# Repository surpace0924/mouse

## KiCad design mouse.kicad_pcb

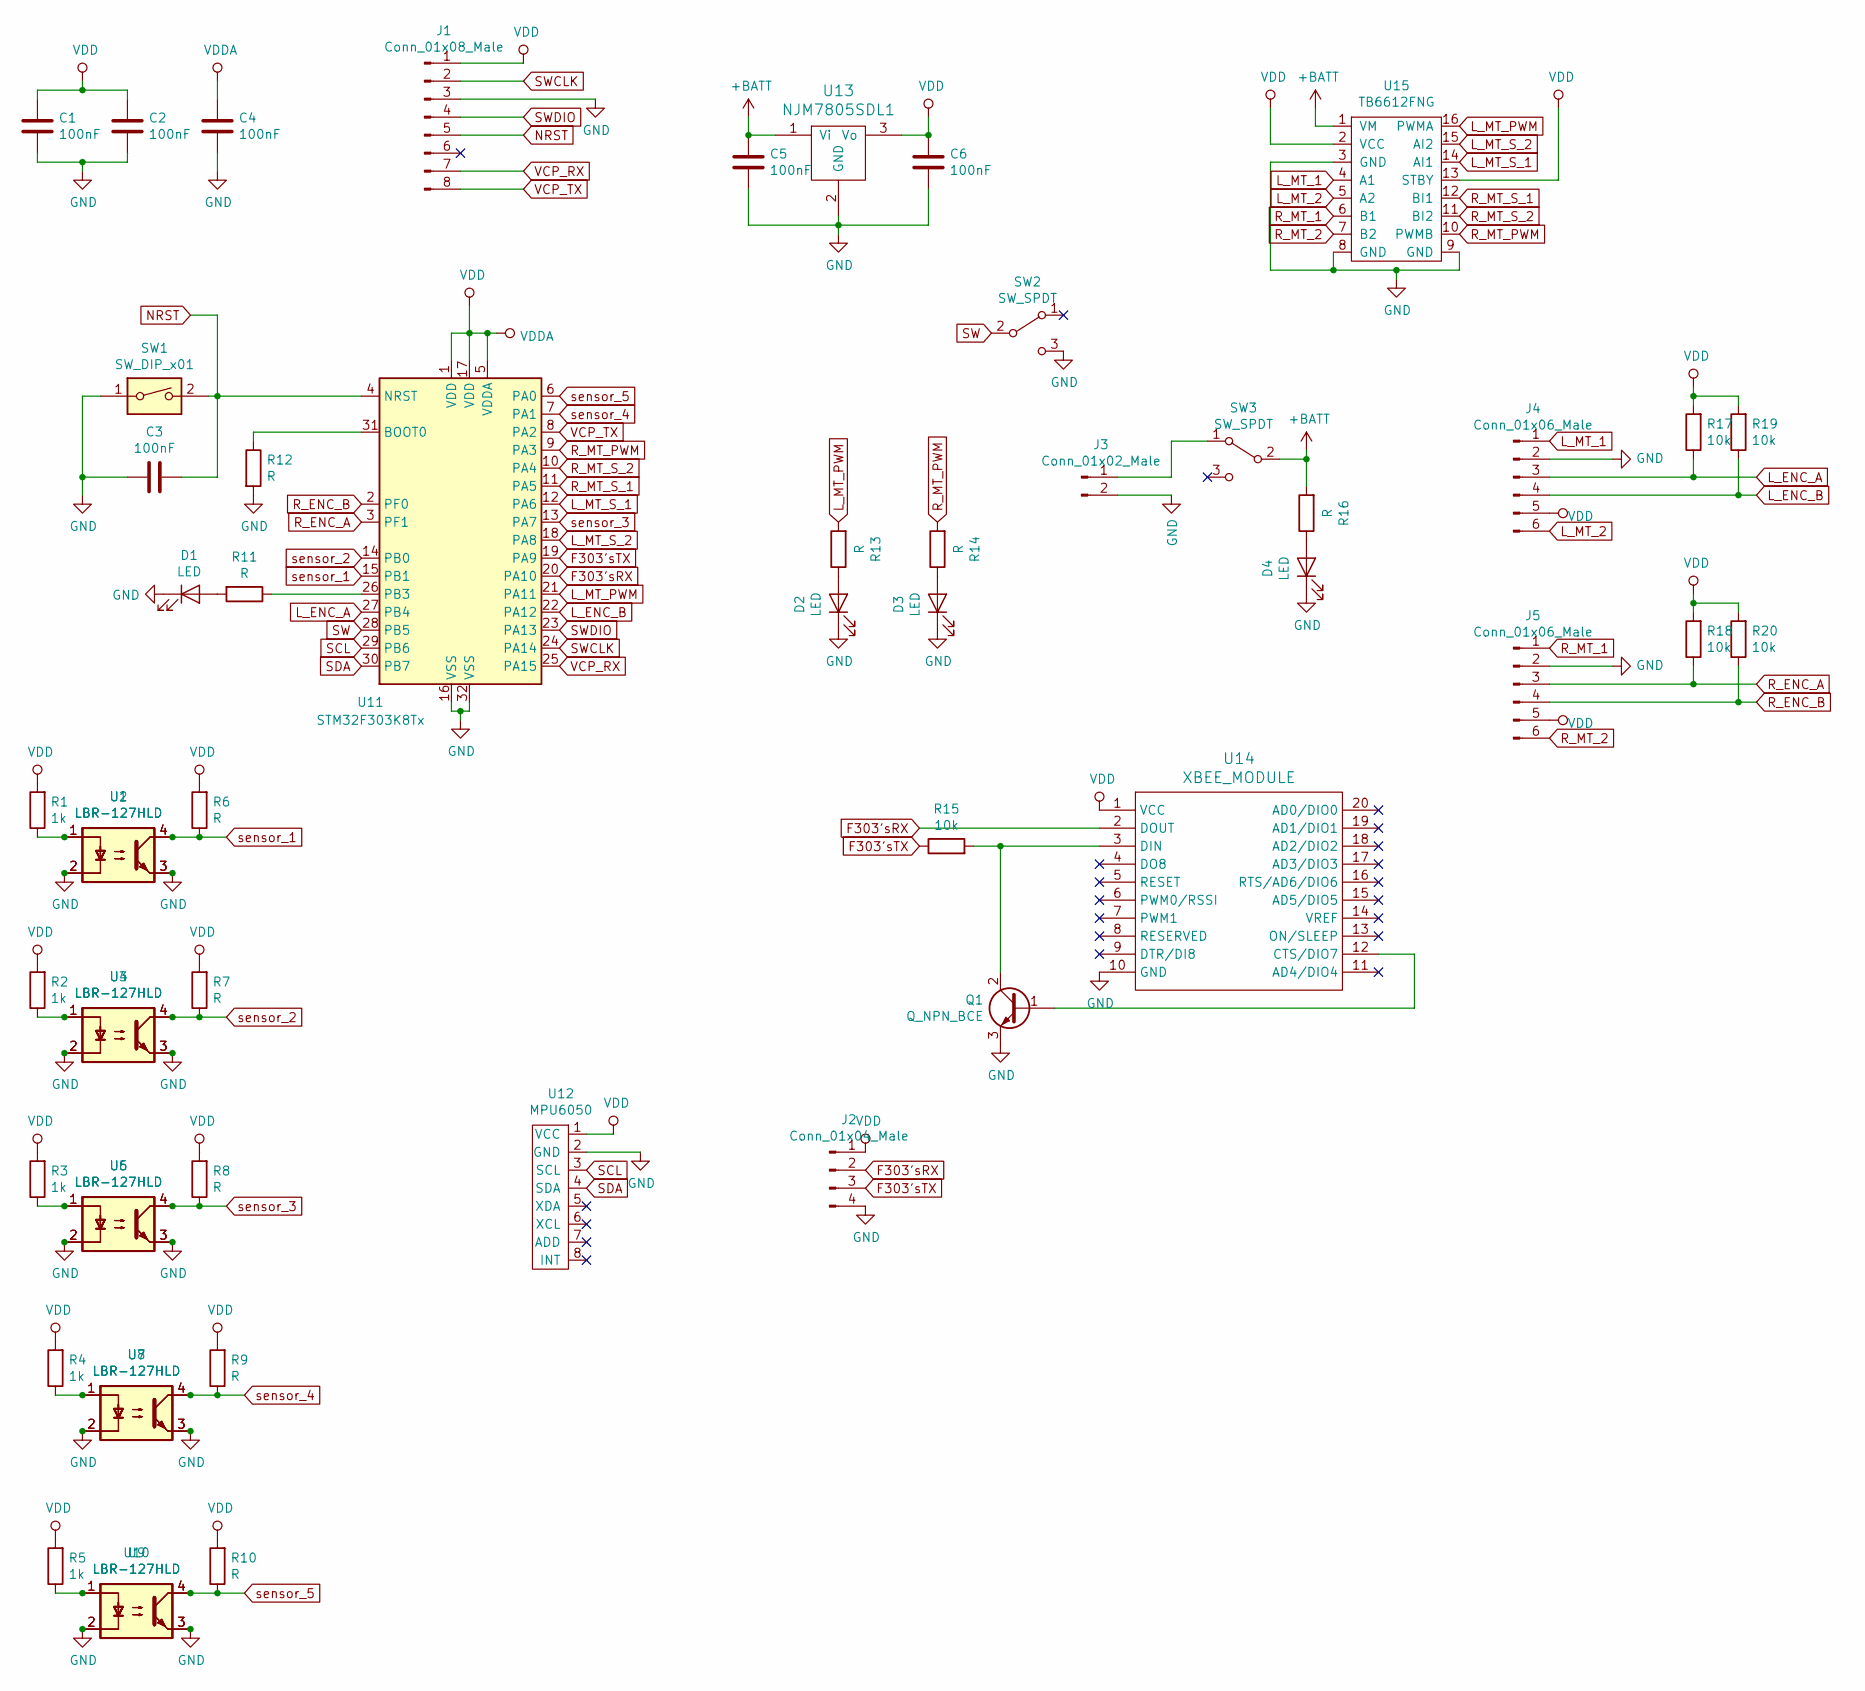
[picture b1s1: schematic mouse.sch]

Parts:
C1, C2, C3, C4, C5, C6: 100nF; C_0805_2012Metric_Pad1.15x1.40mm_HandSolder
D1, D2, D3, D4: LED; LED_0603_1608Metric
J1: Conn_01x08_Male; PinSocket_1x08_P2.54mm_Vertical
J2: Conn_01x04_Male; JST_XH_B4B-XH-A_1x04_P2.50mm_Vertical
J3: Conn_01x02_Male; JST_XH_B2B-XH-A_1x02_P2.50mm_Vertical
J4, J5: Conn_01x06_Male; PinSocket_1x06_P2.54mm_Vertical
Q1: Q_NPN_BCE; TO-92Flat
R1, R2, R3, R4, R5: 1k; R_0603_1608Metric_Pad1.05x0.95mm_HandSolder
R6, R7, R8, R9, R10: R; R_Axial_DIN0204_L3.6mm_D1.6mm_P7.62mm_Horizontal
R11, R12, R13, R14, R16: R; R_0603_1608Metric_Pad1.05x0.95mm_HandSolder
R15, R17, R18, R19, R20: 10k; R_0603_1608Metric_Pad1.05x0.95mm_HandSolder
SW1: SW_DIP_x01; SW_PUSH_6mm_H4.3mm
SW2, SW3: SW_SPDT; PinSocket_1x03_P2.54mm_Vertical
U1, U2, U3, U4, U5, U6, U7, U8, U9, U10: LBR-127HLD; LBR-127HLD_2
U11: STM32F303K8Tx; LQFP-32_7x7mm_P0.8mm
U12: MPU6050; MPU6050_2
U13: NJM7805SDL1; TO-252-3_TabPin2
U14: XBEE_MODULE; XBee
U15: TB6612FNG

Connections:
+BATT: C5.2, R16.2, SW3.2 (B), U13.1 (Vi), U15.1 (VM)
F303'sRX: J2.2, U11.20 (PA10), U14.2 (DOUT)
F303'sTX: J2.3, R15.1, U11.19 (PA9)
GND: C1.1, C2.1, C3.2, C4.1, C5.1, C6.1, D1.1 (K), D2.1 (K), D3.1 (K), D4.1 (K), J1.3, J2.4, J3.2, J4.2, J5.2, Q1.3 (E), R12.2, SW1.1, SW2.3 (C), U1.2, U1.3, U2.2, U2.3, U3.2, U3.3, U4.2, U4.3, U5.2, U5.3, U6.2, U6.3, U7.2, U7.3, U8.2, U8.3, U9.2, U9.3, U10.2, U10.3, U11.16 (VSS), U11.32 (VSS), U12.2 (GND), U13.2 (GND), U14.10 (GND), U15.3 (GND), U15.8 (GND), U15.9 (GND)
L_ENC_A: J4.3, R17.1, U11.27 (PB4)
L_ENC_B: J4.4, R19.1, U11.22 (PA12)
L_MT_1: J4.1, U15.4 (A1)
L_MT_2: J4.6, U15.5 (A2)
L_MT_PWM: R13.2, U11.21 (PA11), U15.16 (PWMA)
L_MT_S_1: U11.12 (PA6), U15.14 (AI1)
L_MT_S_2: U11.18 (PA8), U15.15 (AI2)
NRST: C3.1, J1.5, SW1.2, U11.4 (NRST)
unnamed: D1.2 (A), R11.2
unnamed: D2.2 (A), R13.1
unnamed: D3.2 (A), R14.1
unnamed: D4.2 (A), R16.1
unnamed: J3.1, SW3.1 (A)
unnamed: Q1.1 (B), U14.12 (CTS/DIO7)
unnamed: Q1.2 (C), R15.2, U14.3 (DIN)
unnamed: R1.1, U1.1, U2.1
unnamed: R2.1, U3.1, U4.1
unnamed: R3.1, U5.1, U6.1
unnamed: R4.1, U7.1, U8.1
unnamed: R5.1, U9.1, U10.1
unnamed: R11.1, U11.26 (PB3)
unnamed: R12.1, U11.31 (BOOT0)
R_ENC_A: J5.3, R18.1, U11.3 (PF1)
R_ENC_B: J5.4, R20.1, U11.2 (PF0)
R_MT_1: J5.1, U15.6 (B1)
R_MT_2: J5.6, U15.7 (B2)
R_MT_PWM: R14.2, U11.9 (PA3), U15.10 (PWMB)
R_MT_S_1: U11.11 (PA5), U15.12 (BI1)
R_MT_S_2: U11.10 (PA4), U15.11 (BI2)
SCL: U11.29 (PB6), U12.3 (SCL)
SDA: U11.30 (PB7), U12.4 (SDA)
SW: SW2.2 (B), U11.28 (PB5)
SWCLK: J1.2, U11.24 (PA14)
SWDIO: J1.4, U11.23 (PA13)
VCP_RX: J1.7, U11.25 (PA15)
VCP_TX: J1.8, U11.8 (PA2)
VDD: C1.2, C2.2, C4.2, C6.2, J1.1, J2.1, J4.5, J5.5, R1.2, R2.2, R3.2, R4.2, R5.2, R6.2, R7.2, R8.2, R9.2, R10.2, R17.2, R18.2, R19.2, R20.2, U11.1 (VDD), U11.5 (VDDA), U11.17 (VDD), U12.1 (VCC), U13.3 (Vo), U14.1 (VCC), U15.2 (VCC), U15.13 (STBY)
sensor_1: R6.1, U1.4, U2.4, U11.15 (PB1)
sensor_2: R7.1, U3.4, U4.4, U11.14 (PB0)
sensor_3: R8.1, U5.4, U6.4, U11.13 (PA7)
sensor_4: R9.1, U7.4, U8.4, U11.7 (PA1)
sensor_5: R10.1, U9.4, U10.4, U11.6 (PA0)

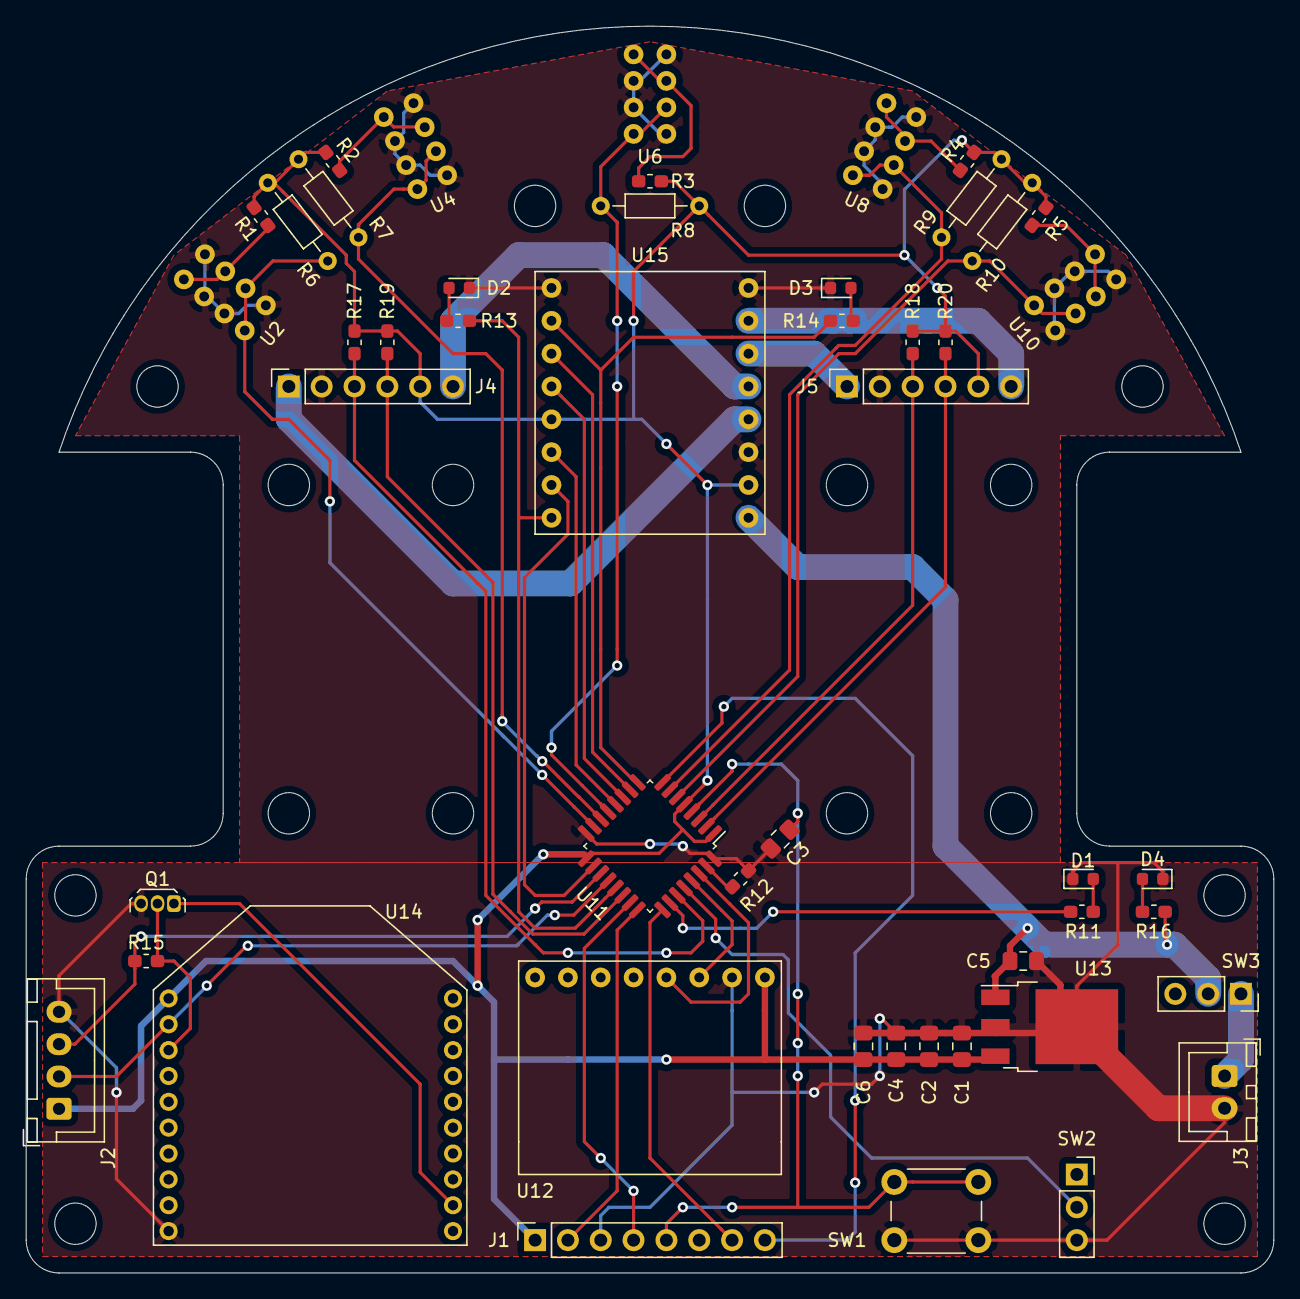
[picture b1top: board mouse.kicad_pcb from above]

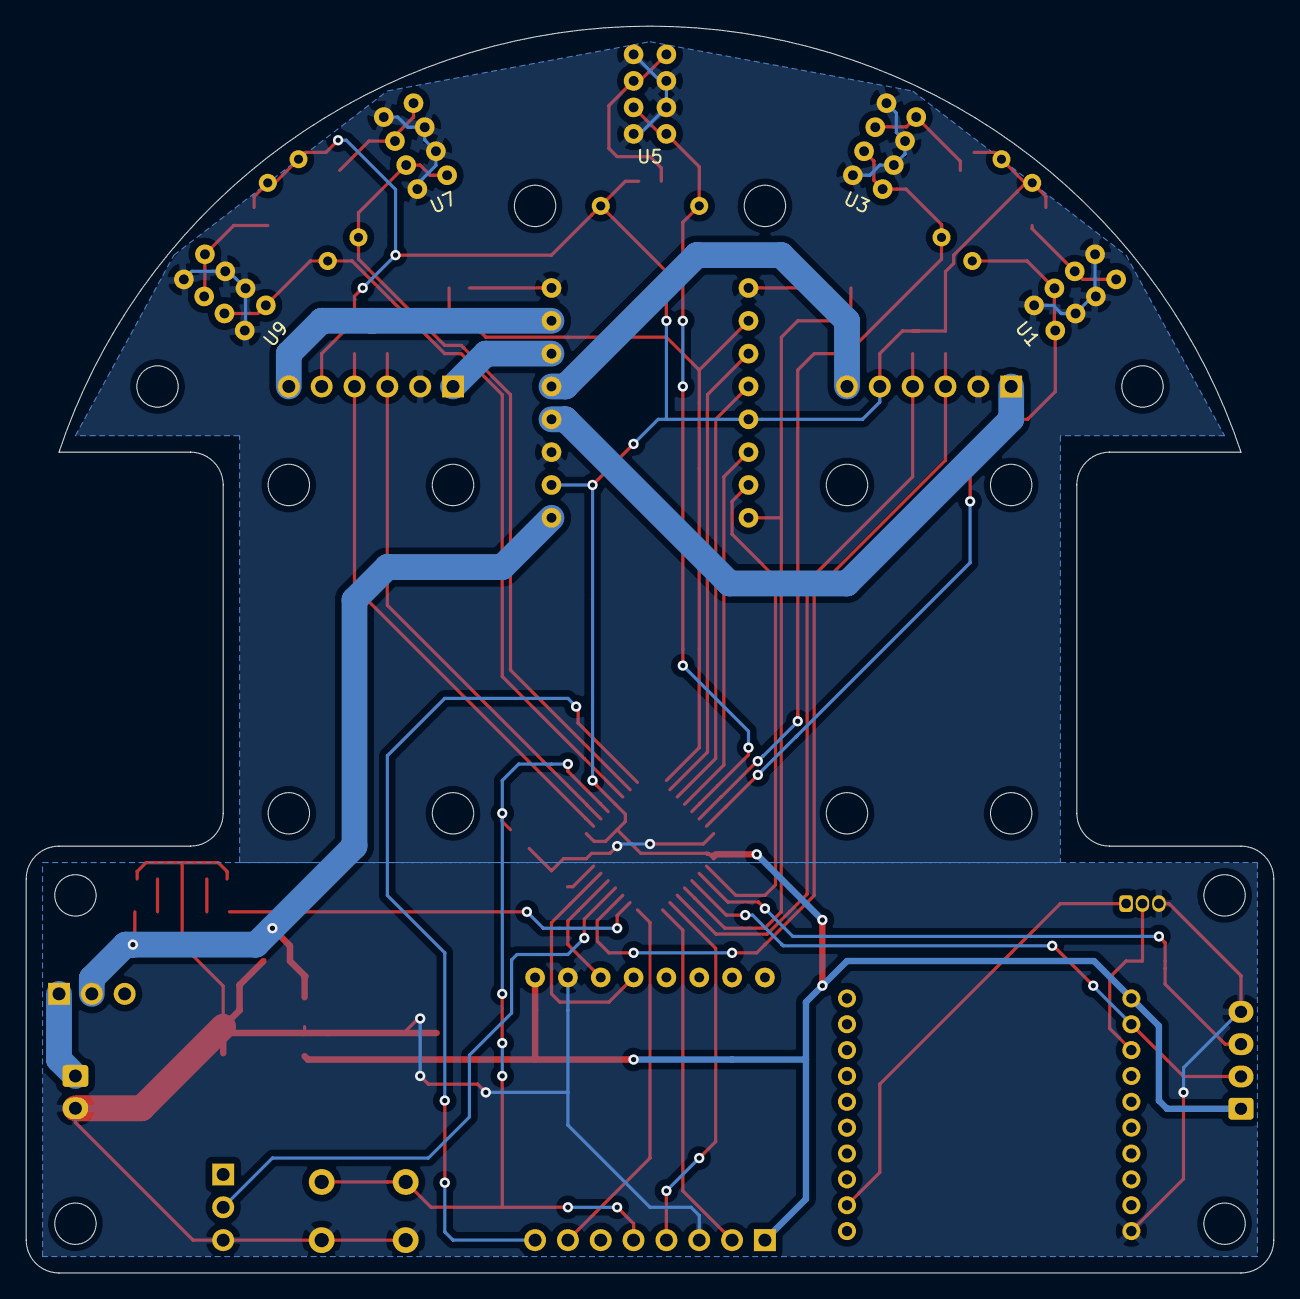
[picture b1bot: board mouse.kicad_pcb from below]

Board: 2 copper layers, 96.5 x 96.5 mm, 70 parts (5 on the bottom side), 46 nets.

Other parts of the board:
 : MountingHole_3.2mm_M3
 #2,  #3,  #4,  #5,  #6,  #7,  #8,  #9,  #10,  #11,  #12,  #13,  #14,  #15,  #16: MountingHole_3.2mm_M3

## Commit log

2020-01-03 update: ver1.0設計
2020-01-03 fix: シルクの修正
2020-01-04 update: ガーバーデータの生成
2020-01-08 update: 色々
